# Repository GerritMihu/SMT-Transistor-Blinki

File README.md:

# SMD Transistor Blinker

## BOM

| Component | Value | Supplier | Link |
| ----------- | ------ | ------- | ---------------------------------- |
| Kondensator | 10µF | Mouser | https://www.mouser.at/ProductDetail/Murata-Electronics/GCM31CD71H106KE36L?qs=By6Nw2ByBD1oHD3I3aH59w%3D%3D |
| Widerstand | 1kΩ | Mouser | https://www.mouser.at/ProductDetail/Bourns/CR0805AFX-1001EAS?qs=mAH9sUMRCtuBEx1SCnbzgg%3D%3D |
| Widerstand | 120kΩ | Mouser |https://www.mouser.at/ProductDetail/Bourns/CR0805-JW-124ELF?qs=sGAEpiMZZMukHu%252BjC5l7YeS2YHLDsUik0yZ2uigiNW8%3D |
| LED | RED | Mouser | https://www.mouser.at/ProductDetail/Lumileds/L150-50805006000H0?qs=MyNHzdoqoQIdcy00zd2cLQ%3D%3D |
| Transistor | BC846 | Mouser |https://www.mouser.at/ProductDetail/Nexperia/BC846215?qs=me8TqzrmIYXkX1bWZY2EVg%3D%3D |

## Leiterplatte / PCBA 

## Schaltung / Circuit

## Bauteileerklärung:

### Widerstände:

Ein Widerstand (R1-R4) ist ein elektronisches Bauteil, das den Stromfluss in einem Stromkreis begrenzt oder reguliert. Er wandelt einen Teil der elektrischen Energie in Wärme um und beeinflusst so, wie viel Strom durch einen bestimmten Teil eines Stromkreises fließen kann.

### Kondensator: 

Ein Kondensator (C1 & C2) ist ein elektronisches Bauteil, das elektrische Energie speichert. Er besteht aus zwei leitfähigen Flächen, den sogenannten Platten, die durch ein Isoliermaterial (das Dielektrikum) voneinander getrennt sind. Die Hauptfunktion eines Kondensators ist es, Ladung zu speichern und bei Bedarf wieder abzugeben.

### LED: 

Eine LED (Light Emitting Diode D1 & D2) ist ein elektronisches Bauteil, das Licht erzeugt, wenn elektrischer Strom durch es hindurchfließt.

### Transistor:

Ein Transistor (Q1 & Q2) ist ein elektronisches Bauteil, das als Schalter oder Verstärker fungiert. Er besteht aus Halbleitermaterialien und hat drei Anschlüsse: Emitter, Basis und Kollektor. Transistoren sind sehr wichtig für die Elektronik, da sie den Stromfluss steuern und Verstärkungsfunktionen ermöglichen.

## Schaltungserklärung:

Die Schaltung basiert auf einem Astabilen Multivibrator, der die beiden Transistoren in einem wechselseitigen Betrieb schaltet. Der erste Transistor (Q1) schaltet die erste LED und der zweite Transistor (Q2) schaltet die zweite LED ein und aus. Dabei wechseln sich die LEDs ab, was das typische „Blinken“ erzeugt.

Ein astabiler Multivibrator ist eine elektronische Schaltung, die ständig zwischen zwei Zuständen hin- und herschaltet, ohne eine externe Steuerung. 

Der J1 ist der Eingang, hier wird die Spannung angelegt. Entweder nimmt man zwei polige Stiftleisten oder einfach zwei Drähte.

## Löten:

### Geräte und Materialen:

Lötstation

Feine Lötspitze für präzises Arbeiten

Lötzinn

Multimeter, das man die Polung und den Wert der Bauteile zuordnen kann

Pinzette

Lötsaugpumpe, Lötsauglitze 

### Ablauf

Sie können dieses HTML Dokument als unterstützung nutzen um hier ihren Fortschritt zu dokumentieren: [BOM](http://htmlpreview.github.io/?https://github.com/GerritMihu/SMT-Transistor-Blinki/blob/main/bom/SMD-Transistor-Blinker-ibom.html)

Lötzinn auf der Platine: Setze eine kleine Menge Lötzinn an einem der Lötpads an, um es vorzubereiten.

Platziere das SMD-Bauteil an der vorgesehenen Stelle auf der Platine mit einer Pinzette. Achte darauf, dass es korrekt ausgerichtet ist (markierte Seiten beachten).

Erhitze das Bauteil: Halte die Spitze des Lötkolbens für ca. 3-10 Sekunden auf das Bauteilbein und das Lötpad. Achte darauf, dass beide Teile warm werden, bevor du das Lötzinn zuführst.

Überprüfe die Lötstelle: Die Lötverbindung sollte glänzend und gleichmäßig sein. Vermeide kalte Lötstellen oder Lötbrücken.

# English:

## Component explanation:

### Resistors:

A resistor (R1-R4) is an electronic component that limits or regulates the flow of current in a circuit. It converts some electrical energy into heat, influencing how much current can flow through a particular part of a circuit.

### Capacitor: 

A capacitor (C1 & C2)is an electronic component that stores electrical energy. It consists of two conductive surfaces, called plates, which are separated from each other by an insulating material (the dielectric). The main function of a capacitor is to store charge and release it when needed.

### LED:

An LED (Light Emitting Diode D1 & D2) is an electronic component that produces light when electric current flows through it.

### Transistor: 

A transistor (Q1 & Q2) is an electronic component that functions as a switch or amplifier. It is made of semiconductor materials and has three connections: emitter, base and collector. Transistors are very important in electronics because they control the flow of current and enable amplification functions.

## Circuit explanation:

The circuit is based on an astable multivibrator that switches the two transistors in alternating operation. The first transistor (Q1) switches the first LED and the second transistor (Q2) switches the second LED on and off. The LEDs alternate, which creates the typical “flashing”.

An astable multivibrator is an electronic circuit that constantly switches between two states without any external control. 

J1 is the input, this is where the voltage is applied. Either you use two-pin pin strips or simply two wires.

## Soldering:

### Equipment and materials:

1. Solderingstation

2. Fine soldering tip for precise work

3. Solder

4. Multimeter, which can be used to determine the polarity and value of the components

5. Tweezers

6. Solder suction pump, solder suction wire

### Soldering on the board:

You can use this dokument to help you with the placement process: [BOM](http://htmlpreview.github.io/?https://github.com/GerritMihu/SMT-Transistor-Blinki/blob/main/bom/SMD-Transistor-Blinker-ibom.html)

Apply a small amount of solder to one of the soldering pads to prepare it.

Place the SMD component in the intended location on the circuit board using tweezers. Make sure it is aligned correctly (note marked sides).

Heat the component: Hold the tip of the soldering iron on the component leg and the soldering pad for approx. 3-10 seconds. Make sure both parts get warm before adding the solder.

Check the solder joint: The solder joint should be shiny and even. Avoid cold solder joints or solder bridges.

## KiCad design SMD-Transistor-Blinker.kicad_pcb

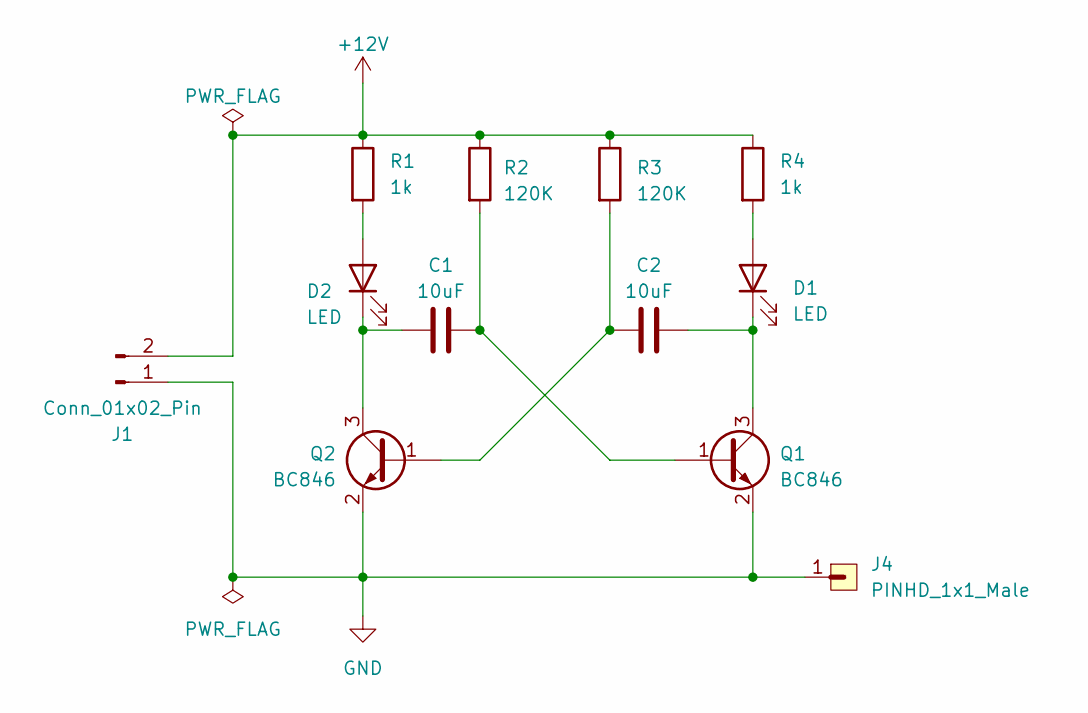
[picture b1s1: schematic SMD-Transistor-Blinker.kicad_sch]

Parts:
C1, C2: 10uF; C_1206_3216Metric_Pad1.33x1.80mm_HandSolder
D1, D2: LED; LED_0805_2012Metric_Pad1.15x1.40mm_HandSolder
J1: Conn_01x02_Pin; PinHeader_1x02_P2.54mm_Vertical
J4: PINHD_1x1_Male; PinHeader_1x01_P2.54mm_Vertical
Q1, Q2: BC846; SOT-23
R1, R4: 1k; R_0805_2012Metric_Pad1.20x1.40mm_HandSolder
R2, R3: 120K; R_0805_2012Metric_Pad1.20x1.40mm_HandSolder

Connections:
+12V: J1.2, R1.1, R2.1, R3.1, R4.1
GND: J1.1, J4.1, Q1.2 (E), Q2.2 (E)
unnamed: D1.2 (A), R4.2
unnamed: C2.2, D1.1 (K), Q1.3 (C)
unnamed: D2.2 (A), R1.2
unnamed: C1.1, D2.1 (K), Q2.3 (C)
unnamed: C1.2, Q1.1 (B), R2.2
unnamed: C2.1, Q2.1 (B), R3.2

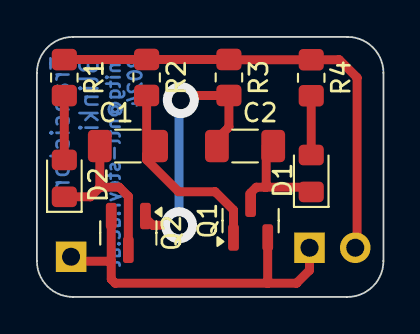
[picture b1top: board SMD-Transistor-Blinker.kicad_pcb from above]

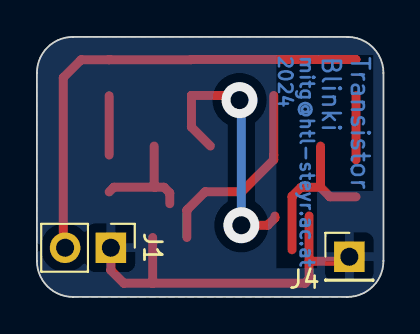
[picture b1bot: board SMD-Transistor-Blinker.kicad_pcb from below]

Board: 2 copper layers, 19.3 x 14.4 mm, 12 parts (2 on the bottom side), 8 nets.

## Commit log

2024-04-18 Added files
2024-04-18 Added QR-Code
2024-04-22 added additional ground pin
2024-05-21 Create #auto_saved_files#
2024-12-10 Readme erstellt
2024-12-10 added Pic of PCB updated PCB & BOM
2024-12-10 Pic in doku
2024-12-10 optimierung kicad
